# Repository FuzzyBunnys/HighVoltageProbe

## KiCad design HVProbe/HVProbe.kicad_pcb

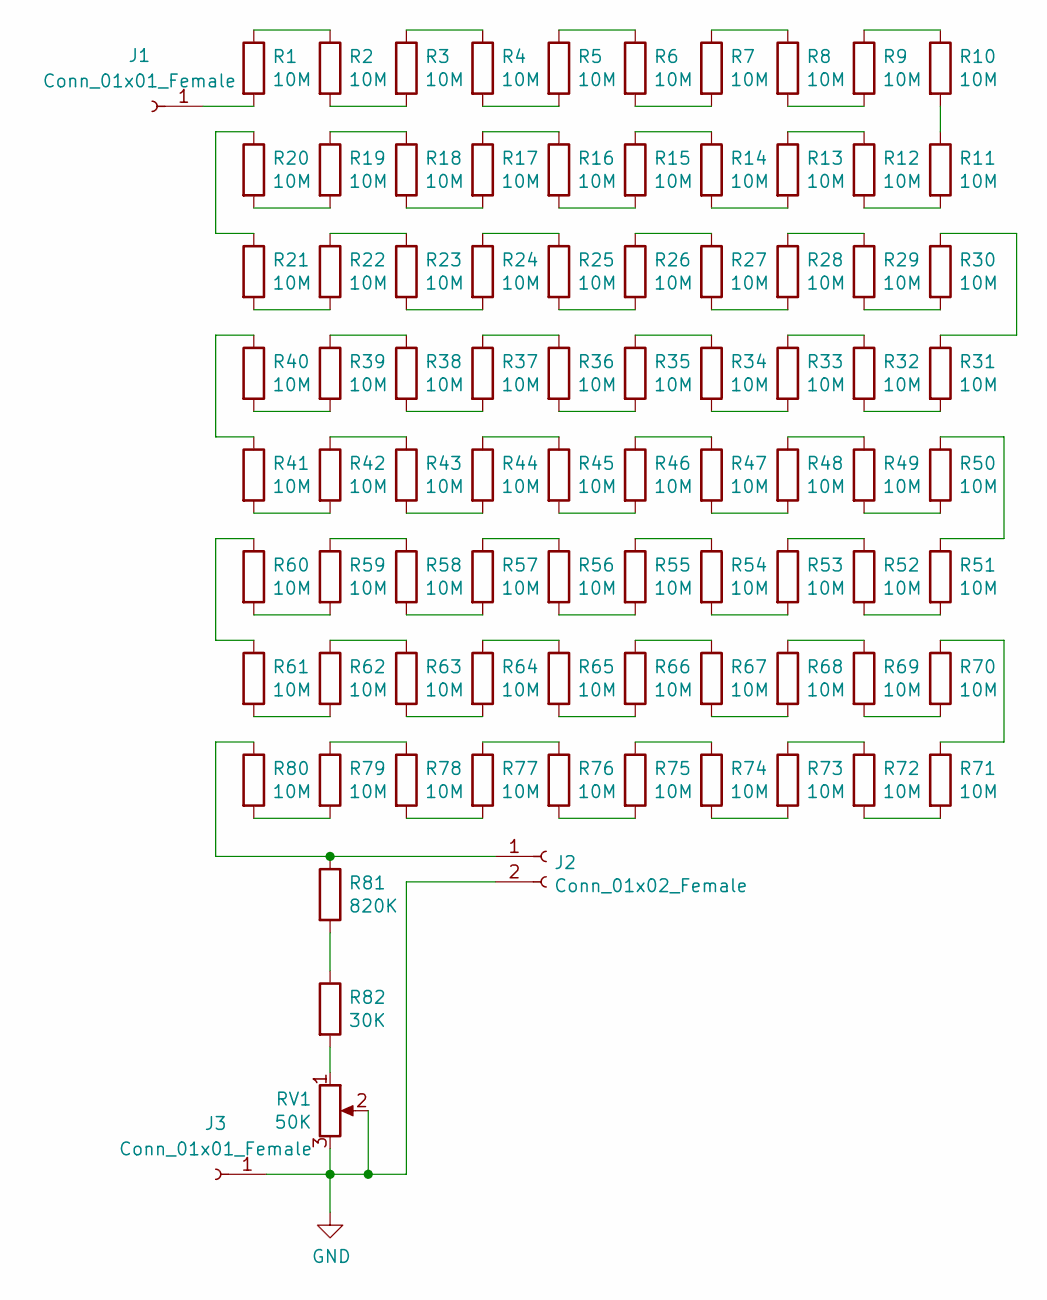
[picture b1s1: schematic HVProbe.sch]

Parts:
J1, J3: Conn_01x01_Female; 1pin
J2: Conn_01x02_Female; Banana_Jack_2Pin
R1, R2, R3, R4, R5, R6, R7, R8, R9, R10, R11, R12, R13, R14, R15, R16, R17, R18, R19, R20, R21, R22, R23, R24, R25, R26, R27, R28, R29, R30, R31, R32, R33, R34, R35, R36, R37, R38, R39, R40, R41, R42, R43, R44, R45, R46, R47, R48, R49, R50, R51, R52, R53, R54, R55, R56, R57, R58, R59, R60, R61, R62, R63, R64, R65, R66, R67, R68, R69, R70, R71, R72, R73, R74, R75, R76, R77, R78, R79, R80: 10M; R_Axial_DIN0411_L9.9mm_D3.6mm_P15.24mm_Horizontal
R81: 820K; R_Axial_DIN0411_L9.9mm_D3.6mm_P15.24mm_Horizontal
R82: 30K; R_Axial_DIN0411_L9.9mm_D3.6mm_P15.24mm_Horizontal
RV1: 50K; Potentiometer_Trimmer_ACP_CA9h2.5_Vertical_Px2.5mm_Py5.0mm

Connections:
GND: J2.2, J3.1, RV1.2, RV1.3
unnamed: J1.1, R1.2
unnamed: J2.1, R80.1, R81.1
unnamed: R1.1, R2.1
unnamed: R2.2, R3.2
unnamed: R3.1, R4.1
unnamed: R4.2, R5.2
unnamed: R5.1, R6.1
unnamed: R6.2, R7.2
unnamed: R7.1, R8.1
unnamed: R8.2, R9.2
unnamed: R9.1, R10.1
unnamed: R10.2, R11.1
unnamed: R11.2, R12.2
unnamed: R12.1, R13.1
unnamed: R13.2, R14.2
unnamed: R14.1, R15.1
unnamed: R15.2, R16.2
unnamed: R16.1, R17.1
unnamed: R17.2, R18.2
unnamed: R18.1, R19.1
unnamed: R19.2, R20.2
unnamed: R20.1, R21.1
unnamed: R21.2, R22.2
unnamed: R22.1, R23.1
unnamed: R23.2, R24.2
unnamed: R24.1, R25.1
unnamed: R25.2, R26.2
unnamed: R26.1, R27.1
unnamed: R27.2, R28.2
unnamed: R28.1, R29.1
unnamed: R29.2, R30.2
unnamed: R30.1, R31.1
unnamed: R31.2, R32.2
unnamed: R32.1, R33.1
unnamed: R33.2, R34.2
unnamed: R34.1, R35.1
unnamed: R35.2, R36.2
unnamed: R36.1, R37.1
unnamed: R37.2, R38.2
unnamed: R38.1, R39.1
unnamed: R39.2, R40.2
unnamed: R40.1, R41.1
unnamed: R41.2, R42.2
unnamed: R42.1, R43.1
unnamed: R43.2, R44.2
unnamed: R44.1, R45.1
unnamed: R45.2, R46.2
unnamed: R46.1, R47.1
unnamed: R47.2, R48.2
unnamed: R48.1, R49.1
unnamed: R49.2, R50.2
unnamed: R50.1, R51.1
unnamed: R51.2, R52.2
unnamed: R52.1, R53.1
unnamed: R53.2, R54.2
unnamed: R54.1, R55.1
unnamed: R55.2, R56.2
unnamed: R56.1, R57.1
unnamed: R57.2, R58.2
unnamed: R58.1, R59.1
unnamed: R59.2, R60.2
unnamed: R60.1, R61.1
unnamed: R61.2, R62.2
unnamed: R62.1, R63.1
unnamed: R63.2, R64.2
unnamed: R64.1, R65.1
unnamed: R65.2, R66.2
unnamed: R66.1, R67.1
unnamed: R67.2, R68.2
unnamed: R68.1, R69.1
unnamed: R69.2, R70.2
unnamed: R70.1, R71.1
unnamed: R71.2, R72.2
unnamed: R72.1, R73.1
unnamed: R73.2, R74.2
unnamed: R74.1, R75.1
unnamed: R75.2, R76.2
unnamed: R76.1, R77.1
unnamed: R77.2, R78.2
unnamed: R78.1, R79.1
unnamed: R79.2, R80.2
unnamed: R81.2, R82.1
unnamed: R82.2, RV1.1

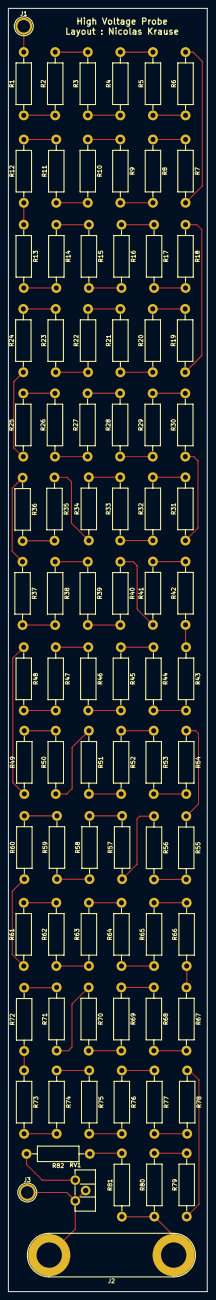
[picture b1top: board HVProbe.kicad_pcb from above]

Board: 2 copper layers, 47.9 x 309.0 mm, 86 parts (0 on the bottom side), 84 nets.

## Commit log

2020-11-14 Add files via upload
    Initial commit with KiCad files
2021-05-13 Set theme jekyll-theme-minimal
